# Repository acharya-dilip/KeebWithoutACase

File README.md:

# KeebWithoutACase 
This is a simple keyboard I'm designing that wwon't use any frame or exerior but will be ready to assemble with the PCB. Like I'll screw 3 PCB's and it'll act like a case, it's jus smth I visualised when I saw some acrylic
sheets stacked together to make a case for a keyboard somewhere. So why not do it out of PCB :3

# Progress I've Made So Far
- Finished everything from designing the board layout 
- Wiring the board adding the breakaway points
- Parts have been chosen that I'll be using

# Things I'm thinking of Doing
- Adding some good silkscreen
- Coding the firmware
- Choosing the switches
- See if my board is structurally integral
- See if instead manual holes I can add some kind of serations

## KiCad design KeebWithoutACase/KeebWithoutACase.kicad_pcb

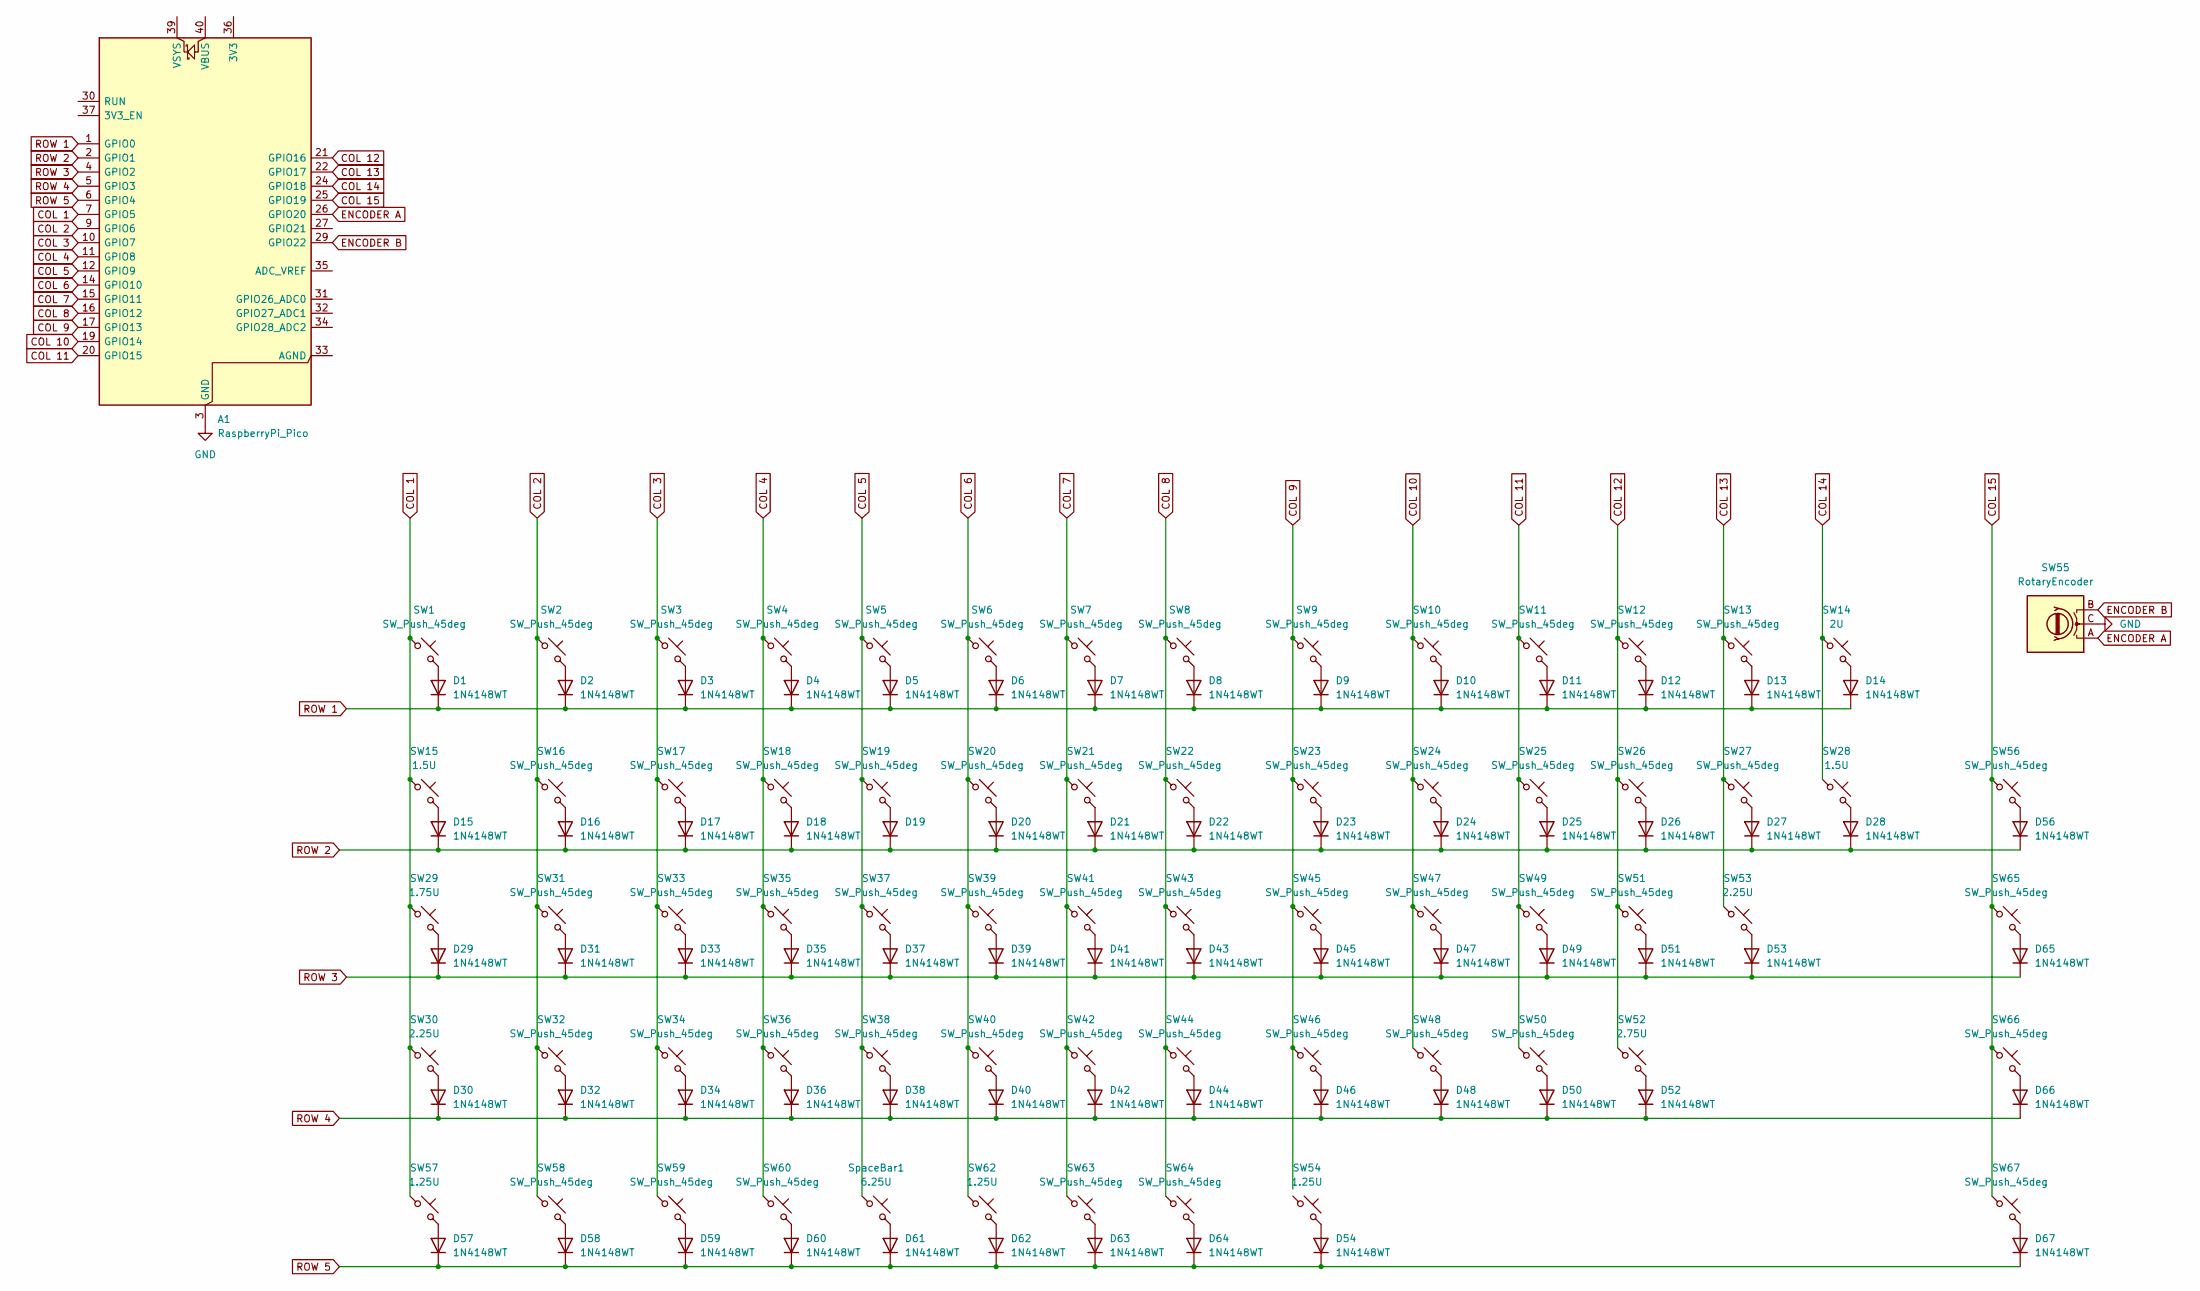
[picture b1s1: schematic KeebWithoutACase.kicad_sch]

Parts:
A1: RaspberryPi_Pico; RaspberryPi_Pico_Common_Unspecified
D1, D2, D3, D4, D5, D6, D7, D8, D9, D10, D11, D12, D13, D14, D15, D16, D17, D18, D20, D21, D22, D23, D24, D25, D26, D27, D28, D29, D30, D31, D32, D33, D34, D35, D36, D37, D38, D39, D40, D41, D42, D43, D44, D45, D46, D47, D48, D49, D50, D51, D52, D53, D54, D56, D57, D58, D59, D60, D61, D62, D63, D64, D65, D66, D67: 1N4148WT; D_DO-27_P15.24mm_Horizontal
D19: D_DO-27_P15.24mm_Horizontal
SW1, SW2, SW3, SW4, SW5, SW6, SW7, SW8, SW9, SW10, SW11, SW12, SW13, SW16, SW17, SW18, SW19, SW20, SW21, SW22, SW23, SW24, SW25, SW26, SW27, SW31, SW32, SW33, SW34, SW35, SW36, SW37, SW38, SW39, SW40, SW41, SW42, SW43, SW44, SW45, SW46, SW47, SW48, SW49, SW50, SW51, SW56, SW58, SW59, SW60, SW63, SW64, SW65, SW66, SW67: SW_Push_45deg; SW_Cherry_MX_1.00u_PCB
SW14: 2U; SW_Cherry_MX_2.00u_PCB
SW15, SW28: 1.5U; SW_Cherry_MX_1.50u_PCB
SW29: 1.75U; SW_Cherry_MX_1.75u_PCB
SW30, SW53: 2.25U; SW_Cherry_MX_2.25u_PCB
SW52: 2.75U; SW_Cherry_MX_2.75u_PCB
SW54, SW57, SW62: 1.25U; SW_Cherry_MX_1.25u_PCB
SW55: RotaryEncoder; RotaryEncoder_Alps_EC11E-Switch_Vertical_H20mm
SpaceBar1: 6.25U; SW_Cherry_MX_6.25u_PCB

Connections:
COL 1: A1.7 (GPIO5), SW1.1, SW15.1, SW29.1, SW30.1, SW57.1
COL 2: A1.9 (GPIO6), SW2.1, SW16.1, SW31.1, SW32.1, SW58.1
COL 3: A1.10 (GPIO7), SW3.1, SW17.1, SW33.1, SW34.1, SW59.1
COL 4: A1.11 (GPIO8), SW4.1, SW18.1, SW35.1, SW36.1, SW60.1
COL 5: A1.12 (GPIO9), SW5.1, SW19.1, SW37.1, SW38.1, SpaceBar1.1
COL 6: A1.14 (GPIO10), SW6.1, SW20.1, SW39.1, SW40.1, SW62.1
COL 7: A1.15 (GPIO11), SW7.1, SW21.1, SW41.1, SW42.1, SW63.1
COL 8: A1.16 (GPIO12), SW8.1, SW22.1, SW43.1, SW44.1, SW64.1
COL 9: A1.17 (GPIO13), SW9.1, SW23.1, SW45.1, SW46.1
COL 10: A1.19 (GPIO14), SW10.1, SW24.1, SW47.1, SW48.1
COL 11: A1.20 (GPIO15), SW11.1, SW25.1, SW49.1, SW50.1
COL 12: A1.21 (GPIO16), SW12.1, SW26.1, SW51.1, SW52.1
COL 13: A1.22 (GPIO17), SW13.1, SW27.1, SW53.1
COL 14: A1.24 (GPIO18), SW14.1, SW28.1
COL 15: A1.25 (GPIO19), SW56.1, SW65.1, SW66.1, SW67.1
ENCODER A: A1.26 (GPIO20), SW55.A
ENCODER B: A1.29 (GPIO22), SW55.B
GND: A1.3 (GND), A1.8 (GND), A1.13 (GND), A1.18 (GND), A1.23 (GND), A1.28 (GND), A1.38 (GND), SW55.C
unnamed: D1.2 (A), SW1.2
unnamed: D2.2 (A), SW2.2
unnamed: D3.2 (A), SW3.2
unnamed: D4.2 (A), SW4.2
unnamed: D5.2 (A), SW5.2
unnamed: D6.2 (A), SW6.2
unnamed: D7.2 (A), SW7.2
unnamed: D8.2 (A), SW8.2
unnamed: D9.2 (A), SW9.2
unnamed: D10.2 (A), SW10.2
unnamed: D11.2 (A), SW11.2
unnamed: D12.2 (A), SW12.2
unnamed: D13.2 (A), SW13.2
unnamed: D14.2 (A), SW14.2
unnamed: D15.2 (A), SW15.2
unnamed: D16.2 (A), SW16.2
unnamed: D17.2 (A), SW17.2
unnamed: D18.2 (A), SW18.2
unnamed: D19.2 (A), SW19.2
unnamed: D20.2 (A), SW20.2
unnamed: D21.2 (A), SW21.2
unnamed: D22.2 (A), SW22.2
unnamed: D23.2 (A), SW23.2
unnamed: D24.2 (A), SW24.2
unnamed: D25.2 (A), SW25.2
unnamed: D26.2 (A), SW26.2
unnamed: D27.2 (A), SW27.2
unnamed: D28.2 (A), SW28.2
unnamed: D29.2 (A), SW29.2
unnamed: D30.2 (A), SW30.2
unnamed: D31.2 (A), SW31.2
unnamed: D32.2 (A), SW32.2
unnamed: D33.2 (A), SW33.2
unnamed: D34.2 (A), SW34.2
unnamed: D35.2 (A), SW35.2
unnamed: D36.2 (A), SW36.2
unnamed: D37.2 (A), SW37.2
unnamed: D38.2 (A), SW38.2
unnamed: D39.2 (A), SW39.2
unnamed: D40.2 (A), SW40.2
unnamed: D41.2 (A), SW41.2
unnamed: D42.2 (A), SW42.2
unnamed: D43.2 (A), SW43.2
unnamed: D44.2 (A), SW44.2
unnamed: D45.2 (A), SW45.2
unnamed: D46.2 (A), SW46.2
unnamed: D47.2 (A), SW47.2
unnamed: D48.2 (A), SW48.2
unnamed: D49.2 (A), SW49.2
unnamed: D50.2 (A), SW50.2
unnamed: D51.2 (A), SW51.2
unnamed: D52.2 (A), SW52.2
unnamed: D53.2 (A), SW53.2
unnamed: D54.2 (A), SW54.2
unnamed: D56.2 (A), SW56.2
unnamed: D57.2 (A), SW57.2
unnamed: D58.2 (A), SW58.2
unnamed: D59.2 (A), SW59.2
unnamed: D60.2 (A), SW60.2
unnamed: D61.2 (A), SpaceBar1.2
unnamed: D62.2 (A), SW62.2
unnamed: D63.2 (A), SW63.2
unnamed: D64.2 (A), SW64.2
unnamed: D65.2 (A), SW65.2
unnamed: D66.2 (A), SW66.2
unnamed: D67.2 (A), SW67.2
ROW 1: A1.1 (GPIO0), D1.1 (K), D2.1 (K), D3.1 (K), D4.1 (K), D5.1 (K), D6.1 (K), D7.1 (K), D8.1 (K), D9.1 (K), D10.1 (K), D11.1 (K), D12.1 (K), D13.1 (K), D14.1 (K)
ROW 2: A1.2 (GPIO1), D15.1 (K), D16.1 (K), D17.1 (K), D18.1 (K), D19.1 (K), D20.1 (K), D21.1 (K), D22.1 (K), D23.1 (K), D24.1 (K), D25.1 (K), D26.1 (K), D27.1 (K), D28.1 (K), D56.1 (K)
ROW 3: A1.4 (GPIO2), D29.1 (K), D31.1 (K), D33.1 (K), D35.1 (K), D37.1 (K), D39.1 (K), D41.1 (K), D43.1 (K), D45.1 (K), D47.1 (K), D49.1 (K), D51.1 (K), D53.1 (K), D65.1 (K)
ROW 4: A1.5 (GPIO3), D30.1 (K), D32.1 (K), D34.1 (K), D36.1 (K), D38.1 (K), D40.1 (K), D42.1 (K), D44.1 (K), D46.1 (K), D48.1 (K), D50.1 (K), D52.1 (K), D66.1 (K)
ROW 5: A1.6 (GPIO4), D54.1 (K), D57.1 (K), D58.1 (K), D59.1 (K), D60.1 (K), D61.1 (K), D62.1 (K), D63.1 (K), D64.1 (K), D67.1 (K)

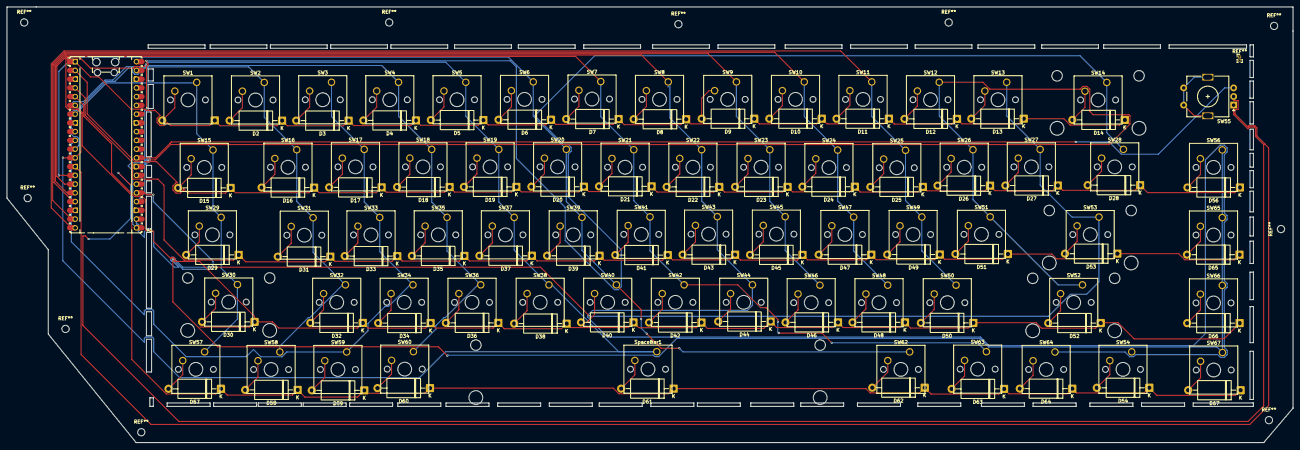
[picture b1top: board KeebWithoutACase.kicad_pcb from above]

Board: 2 copper layers, 373.5 x 126.5 mm, 134 parts (1 on the bottom side), 89 nets.

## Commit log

2026-01-12 finalised and added the keyboard layout to the repo
2026-01-12 added the json file for the keyboard layout to the repo
2026-01-12 completed the first row of switches and diodes
2026-01-12 layed out the switches and diodes for the 2nd and third row
2026-01-12 added the switches and diodes for the final layer
2026-01-12 arranged the keyswitch modules in a way easieer to wire
2026-01-12 wired the matrix for the switches
2026-01-12 added the labels for the 4 rows of the keyboard
2026-01-12 labeled all the columns for the keyboard
2026-01-12 updated the layout and the .json file because silly me forogor to add an entire freakin row of keyboard to the keyboard
2026-01-12 updated the schematic of the pcb to include the missing row
2026-01-12 changed the keyboard layout once again to have 4 media buttons for misc stuff and space for a knob for volume control
2026-01-12 updated the schem to incorporate those extra 4 keys
2026-01-12 added a potentiometer for the volume
2026-01-14 changed the keyboard layout once again and increased some keycaps size to fit the standaard for keycaps size for 60% keyboard
2026-01-14 assigned all the diode footprint and maximum footpprints for the siwtches
2026-01-14 replaced the potentiometer with a rotary encoder and fixed all the footprints for the diodes to be compatible with the ones available near me
2026-01-14 added a placeholder footprint for the rotary encoder
2026-01-14 adjustedd the footprint to match the size of the cherry keys in the schem
2026-01-14 started on the schem
2026-01-15 wired the keeb matrix onto an mcu in the schematic
2026-01-15 completed the first row of keys
2026-01-15 this time completed the first row with the correct keys
2026-01-15 Row 2 complete
2026-01-15 Row 2 complete but i forogt to commit
2026-01-15 completed arranging the third row
2026-01-15 Finished the final forkin row!!!
2026-01-15 finished the media column
2026-01-15 added the diodes for the first row
2026-01-15 added all the diodes fr the 2nd row
2026-01-15 placed rest of the diodes
2026-01-15 unlocekd all the kys for wiring
2026-01-15 wired the switches with their respective diodes
2026-01-15 fixed the schm col1 bleeding
2026-01-15 fixed wiring the switch matrix
2026-01-15 wired all the stuff to the mcu and completed the wiring of the pcb for the keyboard
2026-01-15 wired the pcb cut the edges added serations ettc etc
